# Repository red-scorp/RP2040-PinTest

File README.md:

# RP2040-PinTest Project

The **RP2040-PinTest** project aims to display pin function with a simple LED.

## RP2040-PinTest Board

The **RP2040-PinTest** board is a simple 2-layer intended to test RP2040-Eins and RP2040-ProMini boards.

Preview:

You can view the [Schematics in PDF format](doc/RP2040-PinTest.pdf) for detailed information.

Features:

- Uses Uno and ProMini footprints.
- Inidividual LED for each data pin.

## Version History

### v1.0b1

Initial release for testing purposes.

## How to Help

Your contributions as code, resources, or finances are welcome! Please contact me directly via email at andriy.golovnya@gmail.com or through my [GitHub profile](https://github.com/red-scorp).

If you'd like to make a financial contribution, you can donate via [PayPal](http://paypal.me/redscorp) or [Ko-Fi](http://ko-fi.com/redscorp). Your support is greatly appreciated.

Thanks in advance!

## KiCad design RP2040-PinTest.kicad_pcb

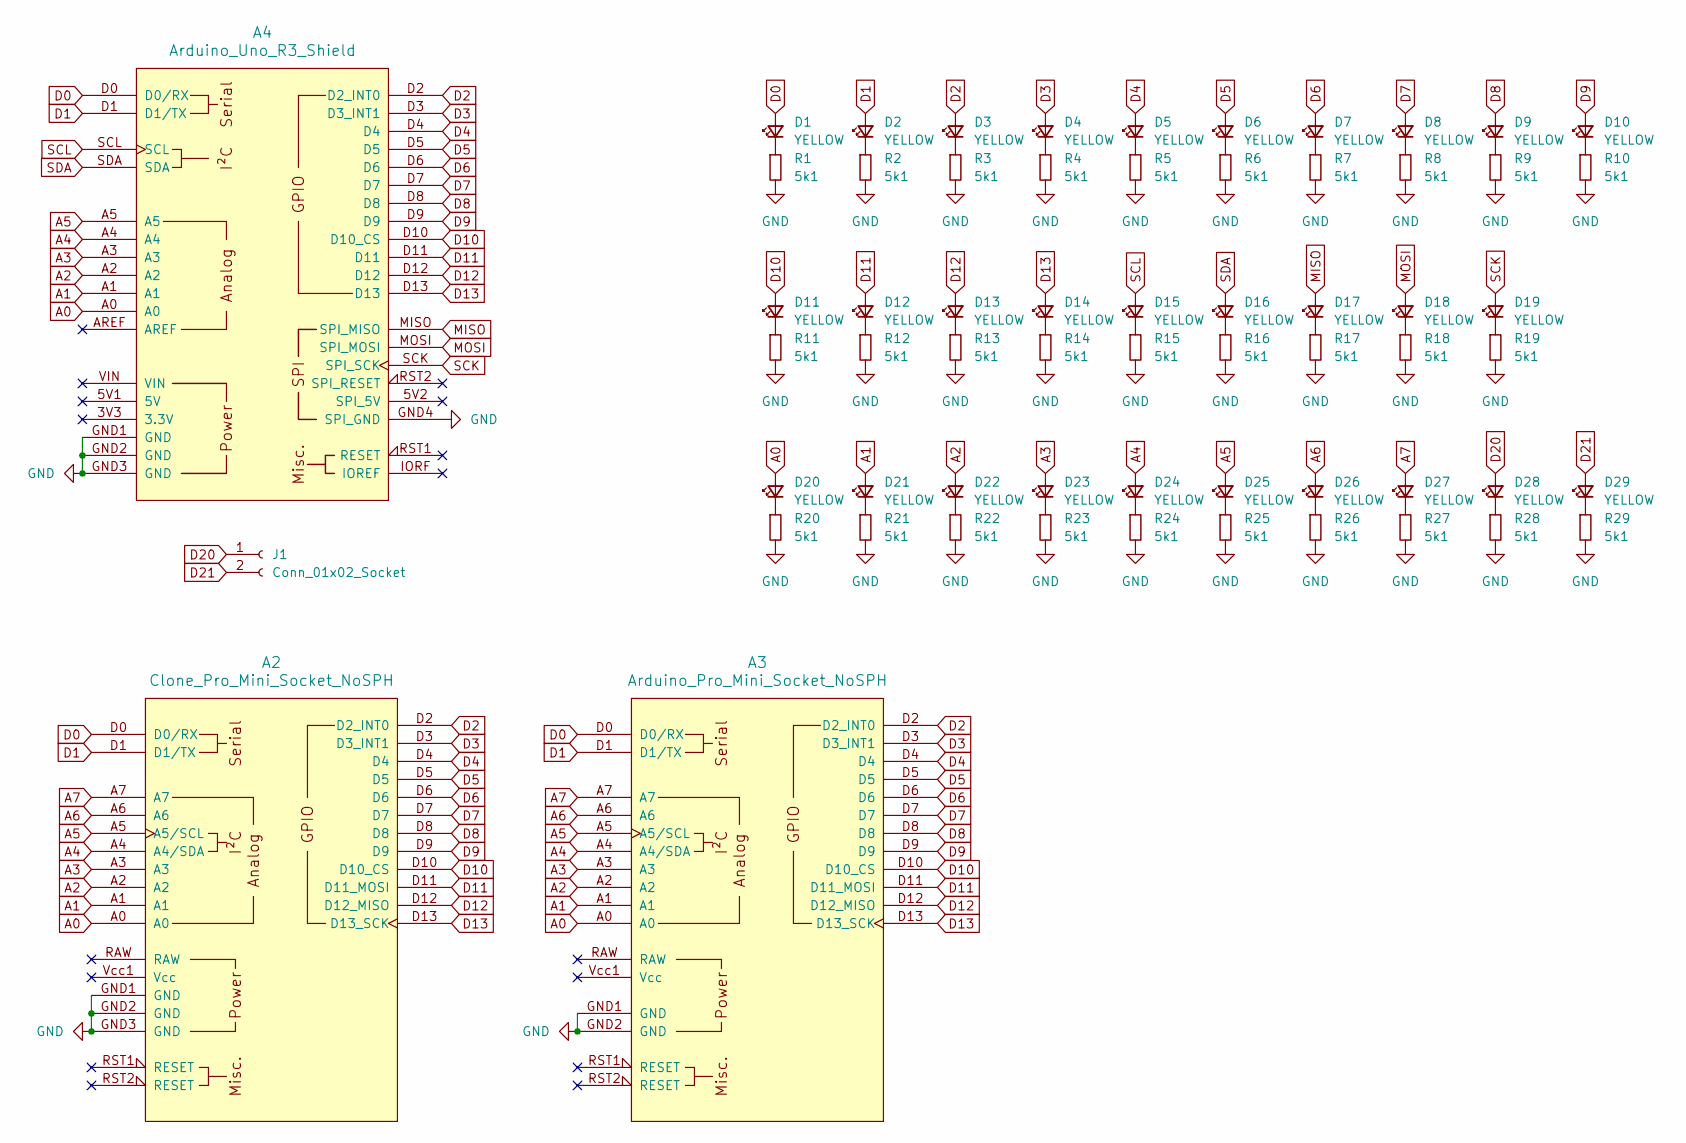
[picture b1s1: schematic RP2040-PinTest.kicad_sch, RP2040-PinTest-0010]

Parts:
A2: Clone_Pro_Mini_Socket_NoSPH
A3: Arduino_Pro_Mini_Socket_NoSPH
A4: Arduino_Uno_R3_Shield
D1, D2, D3, D4, D5, D6, D7, D8, D9, D10, D11, D12, D13, D14, D15, D16, D17, D18, D19, D20, D21, D22, D23, D24, D25, D26, D27, D28, D29: YELLOW; LED_0603_1608Metric
J1: Conn_01x02_Socket; PinSocket_1x02_P2.54mm_Vertical
R1, R2, R3, R4, R5, R6, R7, R8, R9, R10, R11, R12, R13, R14, R15, R16, R17, R18, R19, R20, R21, R22, R23, R24, R25, R26, R27, R28, R29: 5k1; R_0603_1608Metric

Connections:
A0: A2.A0, A3.A0, A4.A0, D20.2 (A)
A1: A2.A1, A3.A1, A4.A1, D21.2 (A)
A2: A2.A2, A3.A2, A4.A2, D22.2 (A)
A3: A2.A3, A3.A3, A4.A3, D23.2 (A)
A4: A2.A4 (A4/SDA), A3.A4 (A4/SDA), A4.A4, D24.2 (A)
A5: A2.A5 (A5/SCL), A3.A5 (A5/SCL), A4.A5, D25.2 (A)
A6: A2.A6, A3.A6, D26.2 (A)
A7: A2.A7, A3.A7, D27.2 (A)
D0: A2.D0 (D0/RX), A3.D0 (D0/RX), A4.D0 (D0/RX), D1.2 (A)
D1: A2.D1 (D1/TX), A3.D1 (D1/TX), A4.D1 (D1/TX), D2.2 (A)
D2: A2.D2 (D2_INT0), A3.D2 (D2_INT0), A4.D2 (D2_INT0), D3.2 (A)
D3: A2.D3 (D3_INT1), A3.D3 (D3_INT1), A4.D3 (D3_INT1), D4.2 (A)
D4: A2.D4, A3.D4, A4.D4, D5.2 (A)
D5: A2.D5, A3.D5, A4.D5, D6.2 (A)
D6: A2.D6, A3.D6, A4.D6, D7.2 (A)
D7: A2.D7, A3.D7, A4.D7, D8.2 (A)
D8: A2.D8, A3.D8, A4.D8, D9.2 (A)
D9: A2.D9, A3.D9, A4.D9, D10.2 (A)
D10: A2.D10 (D10_CS), A3.D10 (D10_CS), A4.D10 (D10_CS), D11.2 (A)
D11: A2.D11 (D11_MOSI), A3.D11 (D11_MOSI), A4.D11, D12.2 (A)
D12: A2.D12 (D12_MISO), A3.D12 (D12_MISO), A4.D12, D13.2 (A)
D13: A2.D13 (D13_SCK), A3.D13 (D13_SCK), A4.D13, D14.2 (A)
D20: D28.2 (A), J1.1
D21: D29.2 (A), J1.2
GND: A2.GND1 (GND), A2.GND2 (GND), A2.GND3 (GND), A3.GND1 (GND), A3.GND2 (GND), A4.GND1 (GND), A4.GND2 (GND), A4.GND3 (GND), A4.GND4 (SPI_GND), R1.2, R2.2, R3.2, R4.2, R5.2, R6.2, R7.2, R8.2, R9.2, R10.2, R11.2, R12.2, R13.2, R14.2, R15.2, R16.2, R17.2, R18.2, R19.2, R20.2, R21.2, R22.2, R23.2, R24.2, R25.2, R26.2, R27.2, R28.2, R29.2
MISO: A4.MISO (SPI_MISO), D17.2 (A)
MOSI: A4.MOSI (SPI_MOSI), D18.2 (A)
unnamed: D1.1 (K), R1.1
unnamed: D2.1 (K), R2.1
unnamed: D3.1 (K), R3.1
unnamed: D4.1 (K), R4.1
unnamed: D5.1 (K), R5.1
unnamed: D6.1 (K), R6.1
unnamed: D7.1 (K), R7.1
unnamed: D8.1 (K), R8.1
unnamed: D9.1 (K), R9.1
unnamed: D10.1 (K), R10.1
unnamed: D11.1 (K), R11.1
unnamed: D12.1 (K), R12.1
unnamed: D13.1 (K), R13.1
unnamed: D14.1 (K), R14.1
unnamed: D15.1 (K), R15.1
unnamed: D16.1 (K), R16.1
unnamed: D17.1 (K), R17.1
unnamed: D18.1 (K), R18.1
unnamed: D19.1 (K), R19.1
unnamed: D20.1 (K), R20.1
unnamed: D21.1 (K), R21.1
unnamed: D22.1 (K), R22.1
unnamed: D23.1 (K), R23.1
unnamed: D24.1 (K), R24.1
unnamed: D25.1 (K), R25.1
unnamed: D26.1 (K), R26.1
unnamed: D27.1 (K), R27.1
unnamed: D28.1 (K), R28.1
unnamed: D29.1 (K), R29.1
SCK: A4.SCK (SPI_SCK), D19.2 (A)
SCL: A4.SCL, D15.2 (A)
SDA: A4.SDA, D16.2 (A)

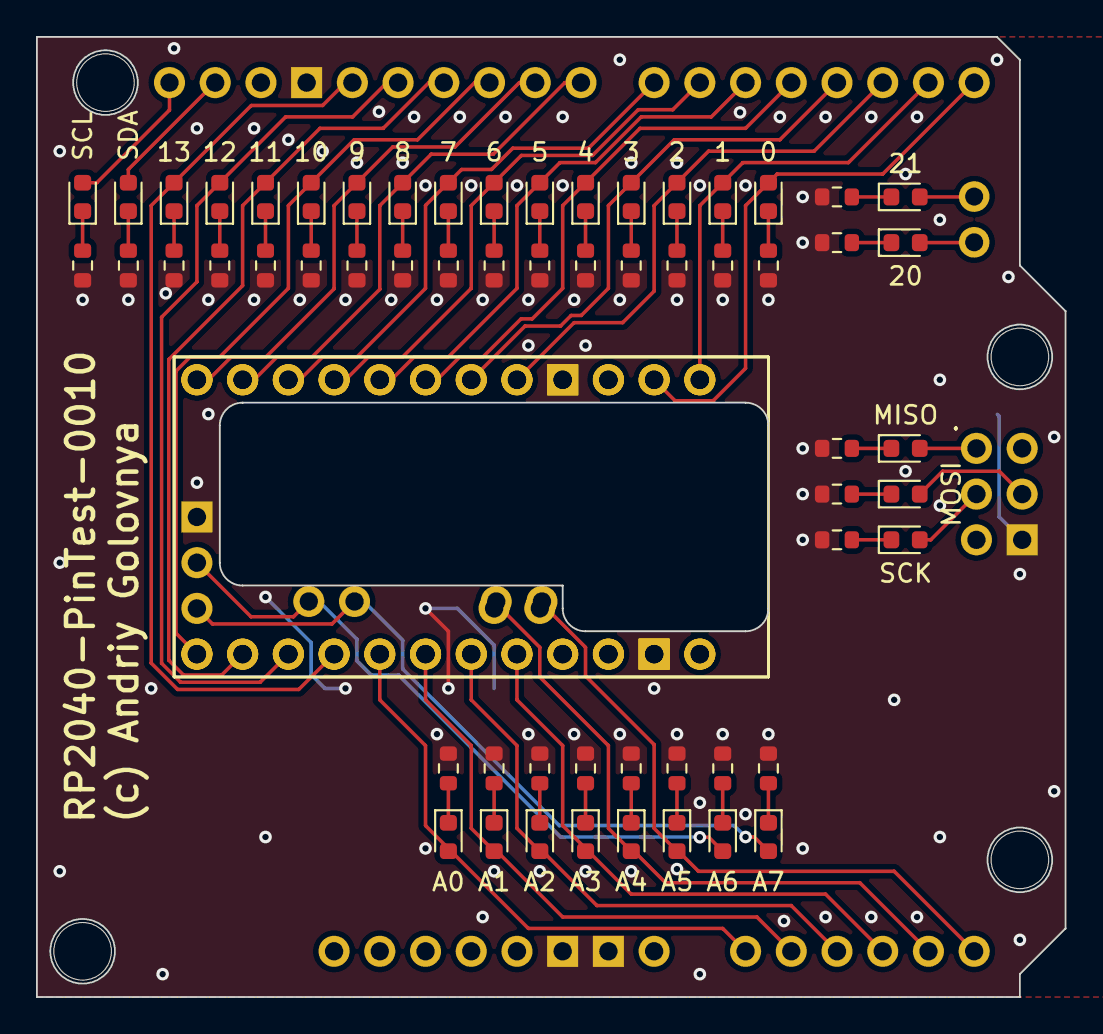
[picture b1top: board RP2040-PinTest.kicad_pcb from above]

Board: 2 copper layers, 57.2 x 53.3 mm, 62 parts (1 on the bottom side), 59 nets.

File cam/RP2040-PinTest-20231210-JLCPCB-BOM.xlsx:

Qty | Designator | Footprint | JLCPCB Part# | Comment
29 | D13,D6,D1,D17,D2,D26,D11,D29,D22,D14,D15,D4,D5,D10,D25,D16,D18,D12,D9,D23,D28,D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 | 0603 | C72038 | YELLOW
29 | R5,R25,R27,R20,R21,R3,R23,R29,R19,R24,R1,R12,R14,R2,R11,R4,R13,R7,R9,R22,R17,R6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 | 0603 | C23186 | 5k1

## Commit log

2023-11-27 First basic design idea
2023-11-28 Added more pins
2023-11-28 Added LEDs and basic routing
2023-11-28 Added few traces and vias
2023-11-28 Added few traces, vias and texts
2023-11-29 Moved stuff around.
2023-12-08 Updated file export parameters
2023-12-08 Generated CAM files
2023-12-08 Generated PDF schematic
2023-12-10 Converted 0.4mm vias to 0.35mm
2023-12-10 Generated BOM and CPL files
2023-12-10 Removed connector's 3D model from the 3D view
2023-12-10 Generated PNG preview
2023-12-10 Added README.md
2023-12-10 Added FUNDING.yml file
2023-12-28 Added basic test program
